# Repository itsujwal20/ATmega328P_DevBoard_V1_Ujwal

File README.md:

# ATmega328P Dev Board V1 - by Ujwal

This is a custom 2-layer development board designed using KiCad around the ATmega328P microcontroller. It includes essential features for easy prototyping, programming, and embedded development.

---

## 📸 Project Preview

### Circuit Diagram

### PCB Layout  

### 3D View  

---

## 🔧 Features

- ✅ ATmega328P Microcontroller (DIP-28)
- ✅ Onboard Power Supply (Barrel Jack Input)
- ✅ 16 MHz Crystal Oscillator with 22pF Capacitors
- ✅ Power LED and RESET Circuit
- ✅ FTDI 6-pin Header for Serial Programming
- ✅ All GPIO Pins Broken Out
- ✅ Decoupling Capacitors (100nF) on VCC/AVCC
- ✅ Ground Plane for Noise Reduction
- ✅ 2-layer PCB Design

---

## 📁 Folder Structure
```
ATmega328P_DevBoard_V1_Ujwal/
├── ATmegafile/
│ ├── schematics/
│ ├── pcb_layout/
│ ├── gerbers/
│ └── ...
├── images/
│ ├── pcb_layout.png
│ └── 3d_view.png
├── README.md
└── LICENSE
```
---

## 🔌 Serial Programming Header (FTDI)

| FTDI Pin | Connects To | Notes                     |
|----------|-------------|---------------------------|
| GND      | GND         | ✔                         |
| VCC      | +5V         | ✔                         |
| TXD      | PD0 (RX)    | MCU RX                    |
| RXD      | PD1 (TX)    | MCU TX                    |
| DTR      | RESET via 100nF | Enables auto-reset   |
| RTS      | (Optional)  | Usually not connected     |

---

## 🛠️ How to Build

1. **Clone this Repo**  
   ```bash
   git clone https://github.com/itsujwal20/ATmega328P_DevBoard_V1_Ujwal.git

2. **Open in KiCad**
   Open the .kicad_pro file from the ATmegafile folder.

3. **Generate Gerbers (Already Included)**
    Use KiCad → File → Plot → Select Layers → Generate Drill Files → ZIP for fabrication.

**🔋 Power Supply Options**
- 5V Regulated Supply via Barrel Jack
- Can also be powered via FTDI (USB to Serial)

**🧪 Applications**
- Embedded systems prototyping
- Arduino-compatible custom projects
- Educational/teaching tool
- Robotics and automation boards

**📝 License**
This project is licensed under the MIT License.
Feel free to fork, modify, and use it commercially or personally.

🙌 Developed by
Ujwal Kumar S
``` https://github.com/itsujwal20 ```

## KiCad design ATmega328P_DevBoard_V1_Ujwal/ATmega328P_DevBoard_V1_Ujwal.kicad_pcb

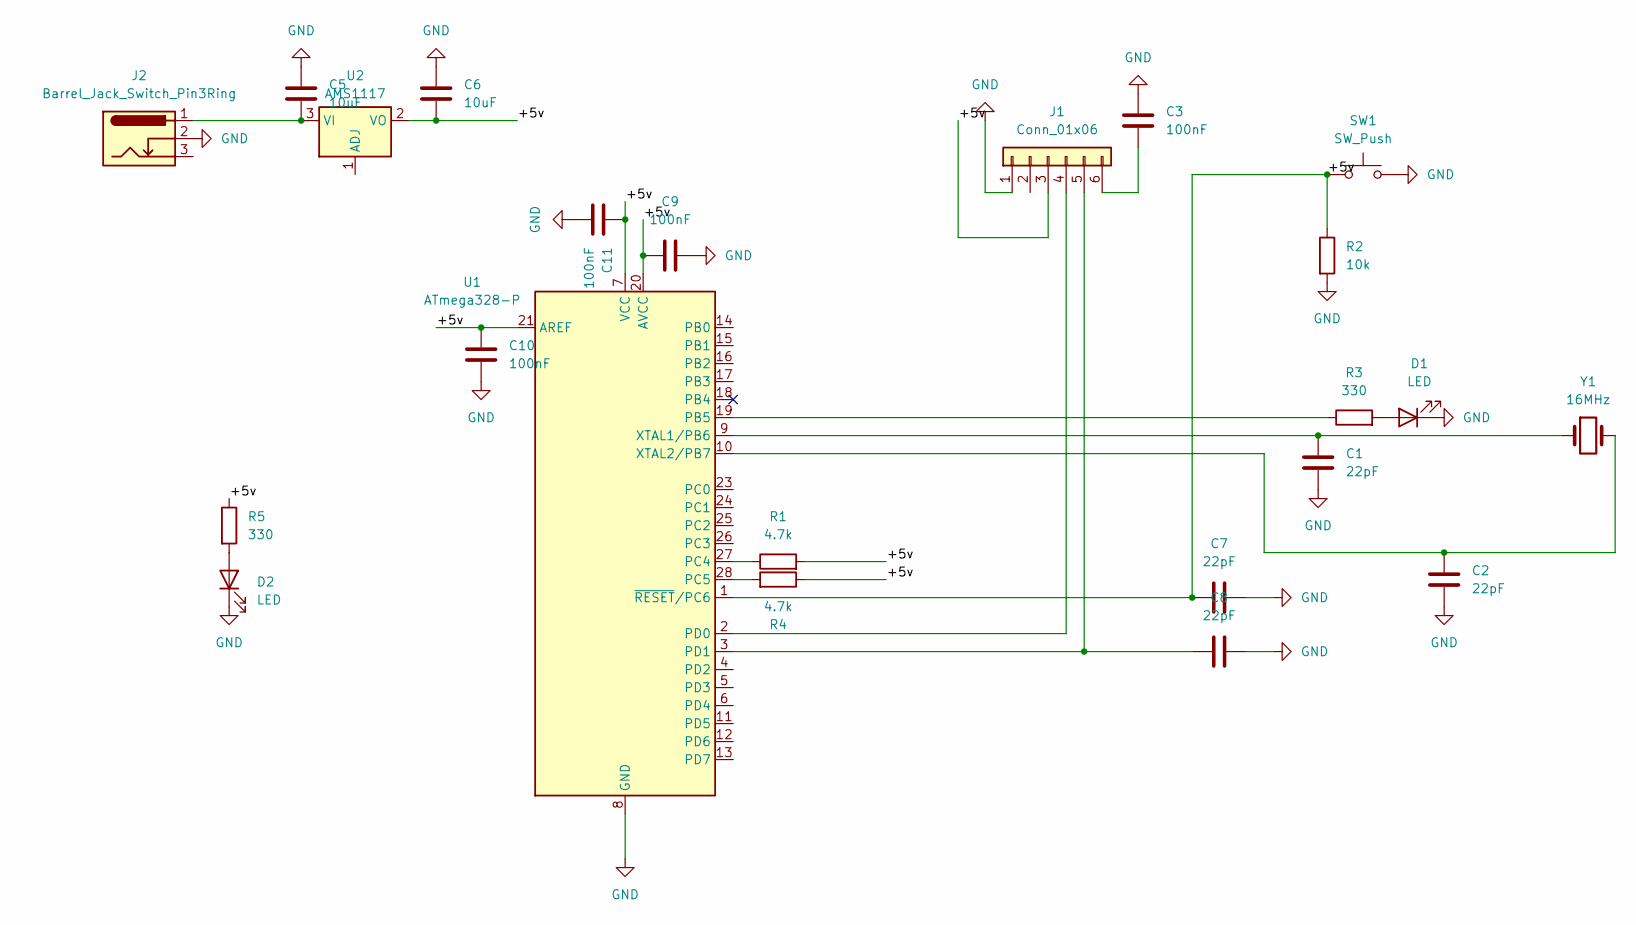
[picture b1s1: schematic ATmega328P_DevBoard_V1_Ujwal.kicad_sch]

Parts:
C1, C2, C7, C8: 22pF; C_Disc_D5.0mm_W2.5mm_P2.50mm
C3, C9, C10, C11: 100nF; C_Disc_D5.0mm_W2.5mm_P2.50mm
C5, C6: 10uF; C_Disc_D5.0mm_W2.5mm_P2.50mm
D1, D2: LED; R_Axial_DIN0207_L6.3mm_D2.5mm_P7.62mm_Horizontal
J1: Conn_01x06; PinHeader_1x06_P2.54mm_Vertical
J2: Barrel_Jack_Switch_Pin3Ring; BarrelJack_Horizontal
R1, R4: 4.7k; R_Axial_DIN0207_L6.3mm_D2.5mm_P7.62mm_Horizontal
R2: 10k; R_Axial_DIN0207_L6.3mm_D2.5mm_P7.62mm_Horizontal
R3, R5: 330; R_Axial_DIN0207_L6.3mm_D2.5mm_P7.62mm_Horizontal
SW1: SW_Push; SW_PUSH_6mm_H5mm
U1: ATmega328-P; DIP-28_W7.62mm
U2: AMS1117; SOT-223-3_TabPin2
Y1: 16MHz; Crystal_HC49-U_Vertical

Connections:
/+5v: C6.2, C7.2, C9.1, C10.1, C11.1, J1.3, R1.2, R2.1, R4.1, R5.1, SW1.1, U1.1 (~RESET/PC6), U1.7 (VCC), U1.20 (AVCC), U1.21 (AREF), U2.2 (VO)
GND: C1.2, C2.2, C3.2, C5.1, C6.1, C7.1, C8.1, C9.2, C10.2, C11.2, D1.1 (K), D2.1 (K), J1.1, J2.2, R2.2, SW1.2, U1.8 (GND), U1.22 (GND)
unnamed: D1.2 (A), R3.2
unnamed: D2.2 (A), R5.2
unnamed: J1.4, U1.2 (PD0)
unnamed: C8.2, J1.5, U1.3 (PD1)
unnamed: C3.1, J1.6
unnamed: R3.1, U1.19 (PB5)
unnamed: R1.1, U1.27 (PC4)
unnamed: R4.2, U1.28 (PC5)
unnamed: C1.1, U1.9 (XTAL1/PB6), Y1.1
unnamed: C2.1, U1.10 (XTAL2/PB7), Y1.2
unnamed: C5.2, J2.1, U2.3 (VI)

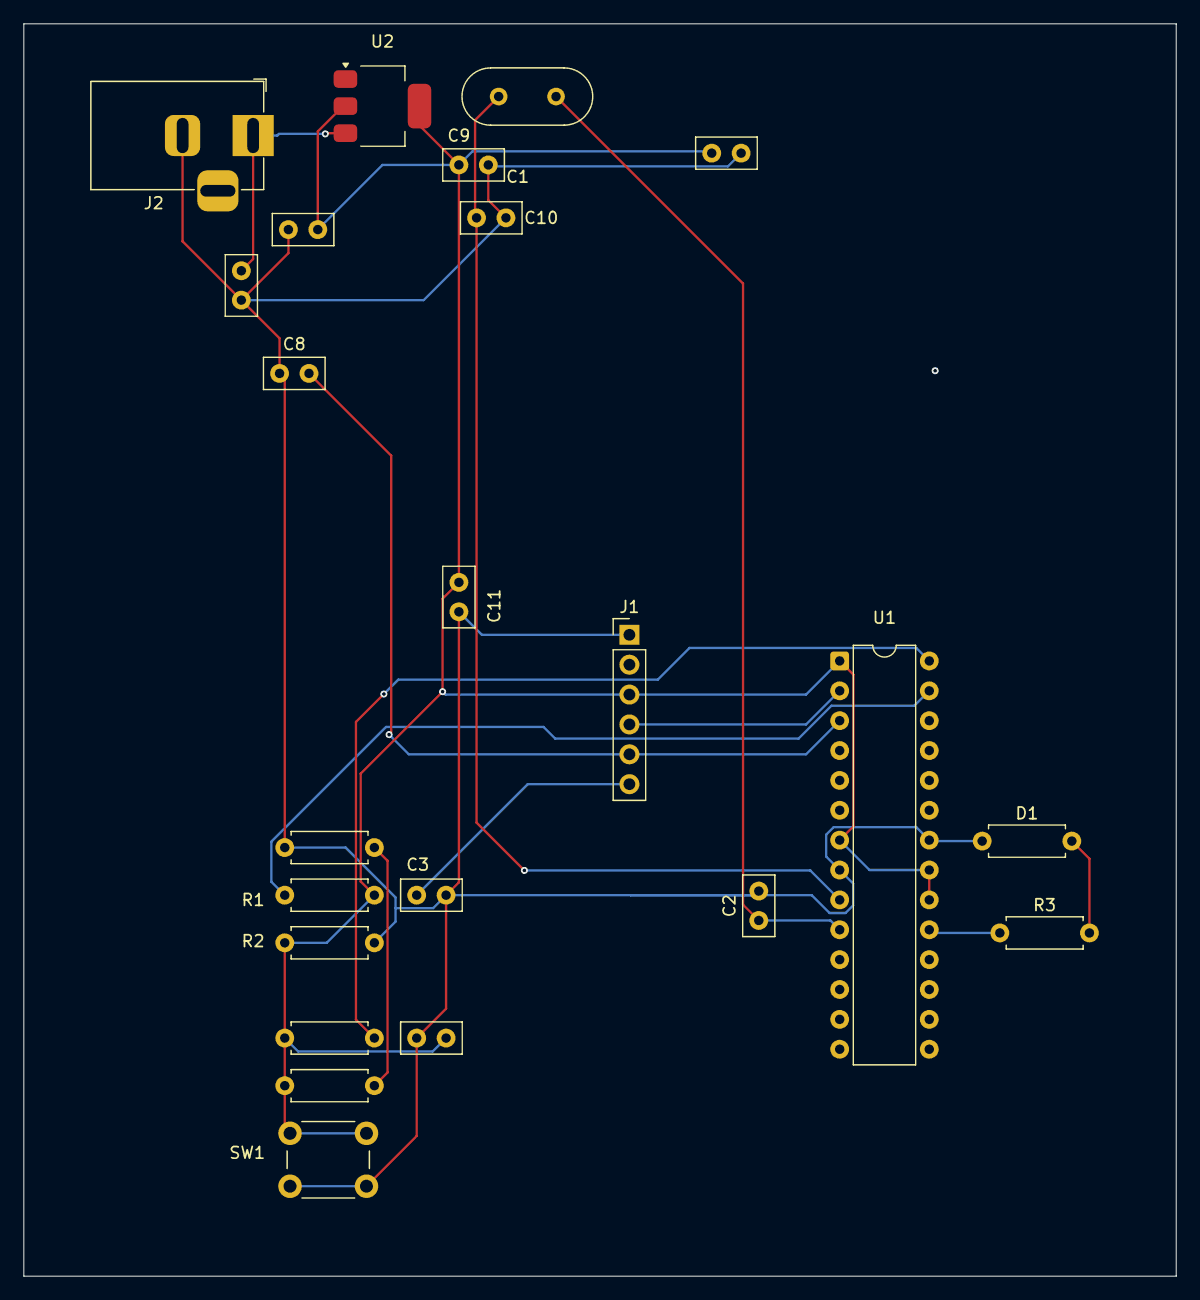
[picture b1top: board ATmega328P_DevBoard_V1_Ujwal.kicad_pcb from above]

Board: 2 copper layers, 98.0 x 106.5 mm, 23 parts (0 on the bottom side), 13 nets.

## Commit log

2025-06-30 Rename PCB_Routing Diagram.png to Pcb_Layout.png
2025-06-30 Rename 3D_View - BACK.png to 3D_View_Back.png
2025-06-30 Rename 3D_View - FRONT.png to 3D_View_Front.png
